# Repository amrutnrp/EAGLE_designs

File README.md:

# EAGLE_designs
Fine, I'll do it myself -Thanos

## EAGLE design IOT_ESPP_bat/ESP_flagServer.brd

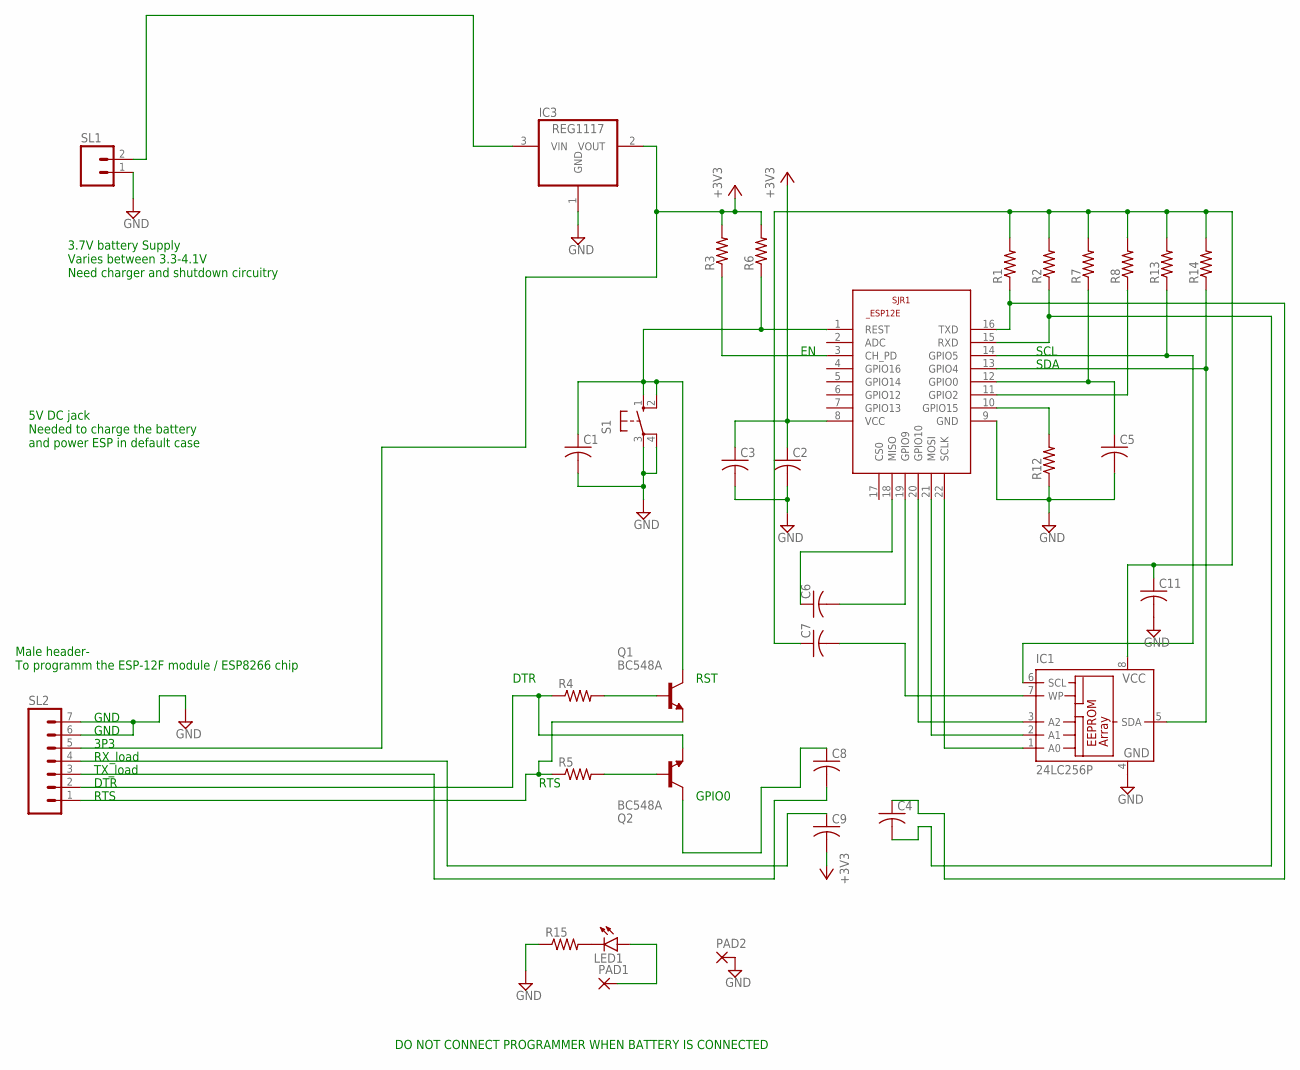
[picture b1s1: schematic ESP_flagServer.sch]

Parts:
C1, C2, C3: C-US050-024X044; C050-024X044
C4, C5, C6, C7, C8, C9, C11: C-US025-024X044; C025-024X044
IC1: 24LC256P; DIL8
IC3: REG1117; SOT223
LED1: LED3MM
PAD1, PAD2: 2,15/1,0
Q1, Q2: BC548A; TO92-EBC
R1, R2, R3, R4, R5, R6, R7, R8, R12, R13, R14, R15: R-US_0204/7; 0204/7
S1: 10-XX; B3F-10XX
SJR1: ESP8266-12EESP12E; ESP8266-ESP12E
SL1: M02; 02P
SL2: M07; 07P

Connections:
+3V3: C2.1, C3.1, C9.2, IC3.2 (VOUT), R3.2, R6.2, SJR1.8 (VCC), SL2.5
GND: C1.2, C2.2, C3.2, C5.2, C11.2, IC1.4 (GND), IC3.1 (GND), PAD2.1, R12.1, R15.1, S1.3, S1.4 (P1), SJR1.9 (GND), SL1.1, SL2.6, SL2.7
unnamed: C4.1, R1.1, SJR1.16 (TXD)
unnamed: Q2.B, R5.2
unnamed: IC1.6 (SCL), R13.1, SJR1.14 (GPIO5)
unnamed: IC1.5 (SDA), R14.1, SJR1.13 (GPIO4)
unnamed: C8.1, Q2.C
unnamed: R8.1, SJR1.11 (GPIO2)
unnamed: R12.2, SJR1.10 (GPIO15)
unnamed: LED1.A, PAD1.1
unnamed: R3.1, SJR1.3 (CH_PD)
unnamed: IC3.3 (VIN), SL1.2
unnamed: IC1.1 (A0), SJR1.22 (SCLK)
unnamed: C1.1, Q1.C, R6.1, S1.1 (S), S1.2 (S1), SJR1.1 (REST)
unnamed: C8.2, SL2.3
unnamed: Q1.B, R4.2
unnamed: Q2.E, R4.1, SL2.2
unnamed: Q1.E, R5.1, SL2.1
unnamed: IC1.2 (A1), SJR1.21 (MOSI)
unnamed: IC1.3 (A2), SJR1.20 (GPIO10)
unnamed: C7.2, IC1.7 (WP)
unnamed: LED1.K (C), R15.2
unnamed: C4.2, R2.1, SJR1.15 (RXD)
unnamed: C6.1, SJR1.18 (MISO)
unnamed: C9.1, SL2.4
unnamed: C5.1, R7.1, SJR1.12 (GPIO0)
unnamed: C6.2, SJR1.19 (GPIO9)
unnamed: C7.1, C11.1, IC1.8 (VCC), R1.2, R2.2, R7.2, R8.2, R13.2, R14.2

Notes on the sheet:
Male header- To programm the ESP-12F module / ESP8266 chip
3.7V battery Supply Varies between 3.3-4.1V Need charger and shutdown circuitry
5V DC jack Needed to charge the battery and power ESP in default case
GND
3P3
RX_load
TX_load
DTR
RTS
RST
GPIO0
DO NOT CONNECT PROGRAMMER WHEN BATTERY IS CONNECTED
SCL
SDA

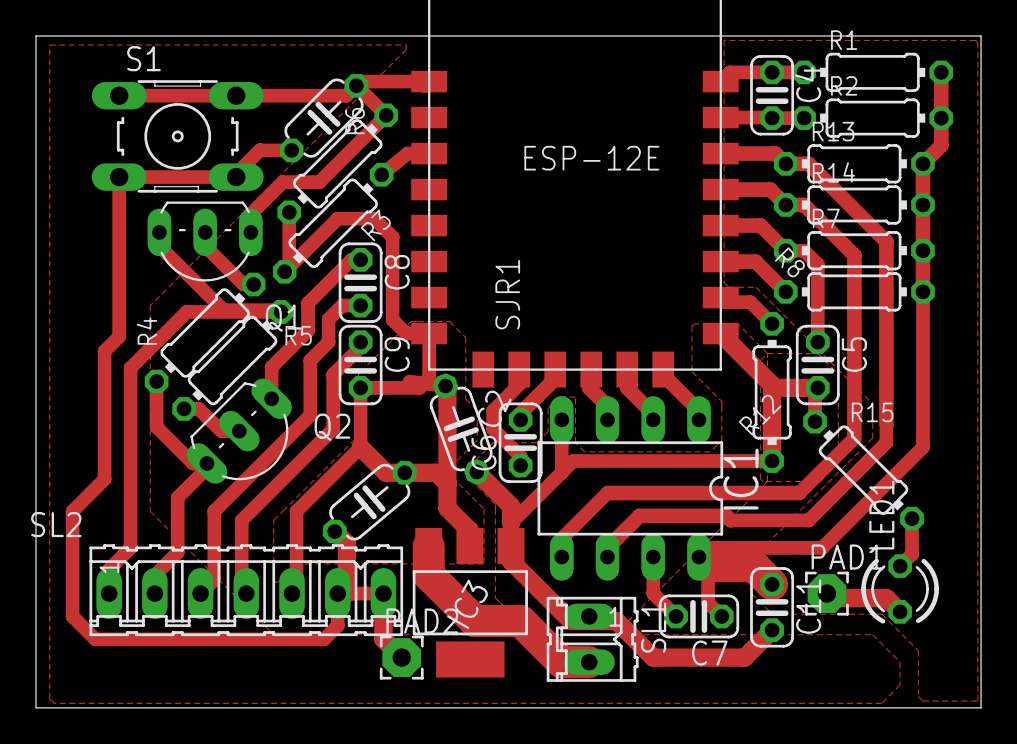
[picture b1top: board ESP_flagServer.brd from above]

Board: 2 copper layers, 52.5 x 37.3 mm, 33 parts (0 on the bottom side), 28 nets.

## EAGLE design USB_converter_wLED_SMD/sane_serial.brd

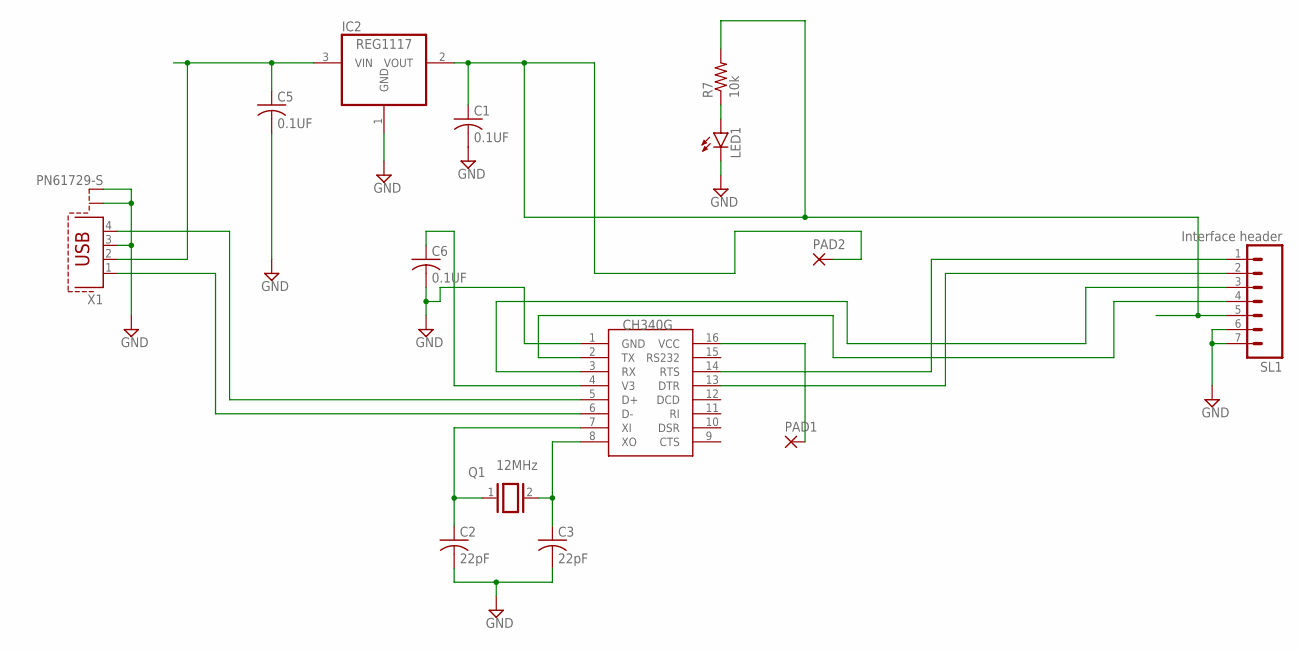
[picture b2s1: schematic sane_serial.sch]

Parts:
C1, C5, C6: 0.1UF; C050-024X044
C2, C3: 22pF; C050-024X044
IC2: REG1117; SOT223
LED1: LED5MM
PAD1, PAD2: 1,6/0,9
Q1: 12MHz; QS
R7: 10k; 0204/7
SL1: Interface header; 07P
U$1: CH340G; SOIC16
X1: PN61729-S

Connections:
GND: C1.2, C2.2, C3.2, C5.2, C6.2, IC2.1 (GND), LED1.K (C), SL1.6, SL1.7, U$1.1 (GND), X1.3, X1.S1, X1.S2
unnamed: U$1.5 (D+), X1.4
unnamed: SL1.2, U$1.13 (DTR)
unnamed: SL1.1, U$1.14 (RTS)
unnamed: SL1.4, U$1.2 (TX)
unnamed: SL1.3, U$1.3 (RX)
unnamed: U$1.6 (D-), X1.1
unnamed: C2.1, Q1.1, U$1.7 (XI)
unnamed: C3.1, Q1.2, U$1.8 (XO)
unnamed: C6.1, U$1.4 (V3)
unnamed: PAD1.1, U$1.16 (VCC)
unnamed: C1.1, IC2.2 (VOUT), PAD2.1, R7.2, SL1.5
unnamed: LED1.A, R7.1
unnamed: C5.1, IC2.3 (VIN), X1.2

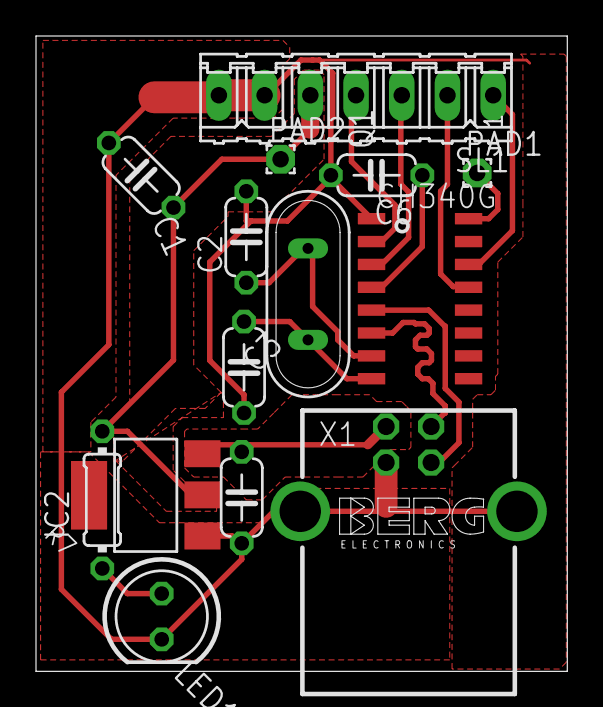
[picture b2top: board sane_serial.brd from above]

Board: 2 copper layers, 29.5 x 35.3 mm, 14 parts (0 on the bottom side), 14 nets.

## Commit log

2021-07-28 first commit
    of PCB stuff...
    -- USB to serial converter --
    -- ESP8266 flag server --
